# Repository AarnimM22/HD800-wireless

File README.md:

view online:
https://kicanvas.org/?repo=https%3A%2F%2Fgithub.com%2FAarnimM22%2FHD800-wireless

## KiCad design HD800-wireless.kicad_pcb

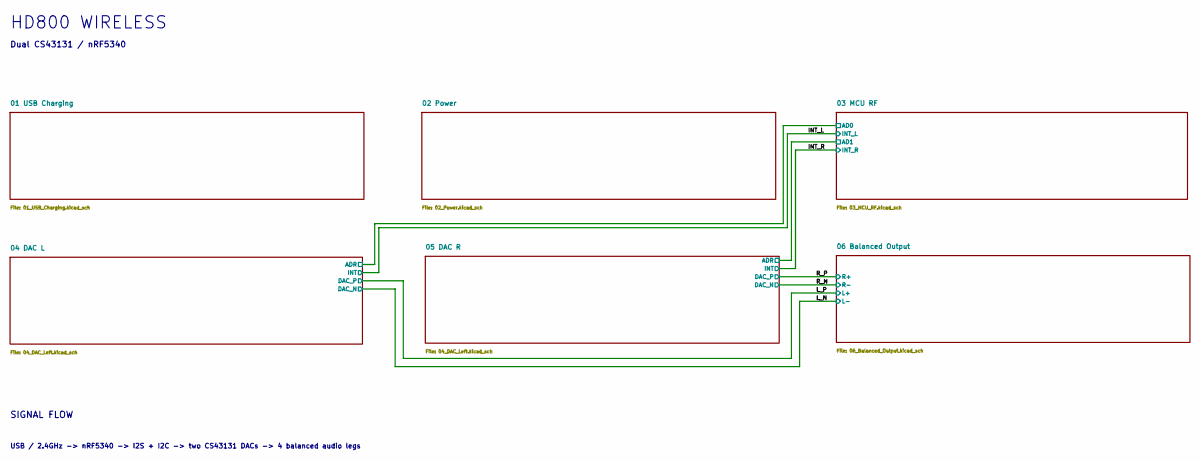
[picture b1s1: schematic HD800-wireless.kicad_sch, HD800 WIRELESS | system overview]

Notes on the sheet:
USB / 2.4GHz -> nRF5340 -> I2S + I2C -> two CS43131 DACs -> 4 balanced audio legs
Dual CS43131 / nRF5340
HD800 WIRELESS
SIGNAL FLOW

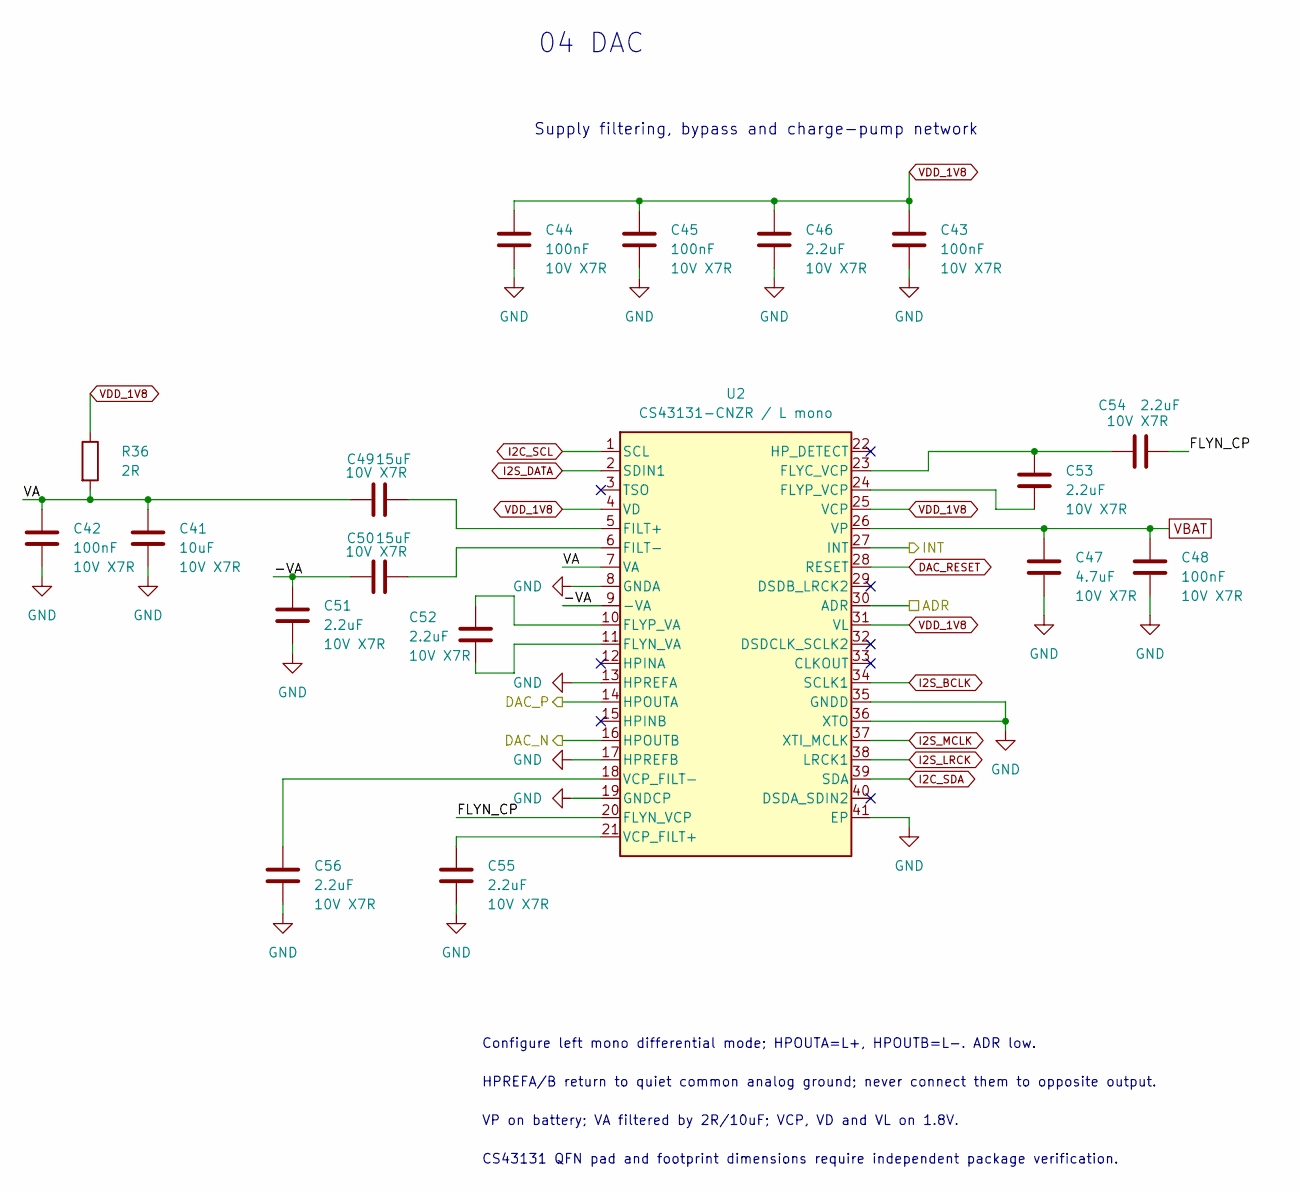
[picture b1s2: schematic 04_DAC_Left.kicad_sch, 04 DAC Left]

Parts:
C41: 10uF; C_0603_1608Metric; Voltage 10V X7R
C42, C43, C44, C45, C48: 100nF; C_0402_1005Metric; Voltage 10V X7R
C46, C51, C52, C53, C54, C55, C56: 2.2uF; C_0402_1005Metric; Voltage 10V X7R
C47: 4.7uF; C_0603_1608Metric; Voltage 10V X7R
C49, C50: 15uF; C_0603_1608Metric; Voltage 10V X7R
R36: 2R; R_0402_1005Metric
U2: CS43131-CNZR / L mono; TQFN-40-1EP_5x5mm_P0.4mm_EP3.5x3.5mm_ThermalVias

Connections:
/04 DAC L/-VA: C50.1, C51.1, U2.9 (-VA)
/04 DAC L/FLYN_CP: C54.2, U2.20 (FLYN_VCP)
/04 DAC L/VA: C41.1, C42.1, C49.1, R36.2, U2.7 (VA)
/INT_L: U2.27 (INT); also elsewhere on the board
/L_N: U2.16 (HPOUTB); also elsewhere on the board
/L_P: U2.14 (HPOUTA); also elsewhere on the board
DAC_RESET: U2.28 (RESET); also elsewhere on the board
GND: C41.2, C42.2, C43.2, C44.2, C45.2, C46.2, C47.2, C48.2, C51.2, C55.2, C56.2, U2.8 (GNDA), U2.13 (HPREFA), U2.17 (HPREFB), U2.19 (GNDCP), U2.30 (ADR), U2.35 (GNDD), U2.36 (XTO), U2.41 (EP); also elsewhere on the board
I2C_SCL: U2.1 (SCL); also elsewhere on the board
I2C_SDA: U2.39 (SDA); also elsewhere on the board
I2S_BCLK: U2.34 (SCLK1); also elsewhere on the board
I2S_DATA: U2.2 (SDIN1); also elsewhere on the board
I2S_LRCK: U2.38 (LRCK1); also elsewhere on the board
I2S_MCLK: U2.37 (XTI_MCLK); also elsewhere on the board
unnamed: C49.2, U2.5 (FILT+)
unnamed: C50.2, U2.6 (FILT-)
unnamed: C53.1, C54.1, U2.23 (FLYC_VCP)
unnamed: C52.2, U2.11 (FLYN_VA)
unnamed: C52.1, U2.10 (FLYP_VA)
unnamed: C53.2, U2.24 (FLYP_VCP)
unnamed: C55.1, U2.21 (VCP_FILT+)
unnamed: C56.1, U2.18 (VCP_FILT-)
VBAT: C47.1, C48.1, U2.26 (VP); also elsewhere on the board
VDD_1V8: C43.1, C44.1, C45.1, C46.1, R36.1, U2.4 (VD), U2.25 (VCP), U2.31 (VL); also elsewhere on the board

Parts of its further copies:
C57, C65, C66, C68, C72: 100nF; C_0402_1005Metric; Voltage 10V X7R
C58: 10uF; C_0603_1608Metric; Voltage 10V X7R
C59, C60, C63, C64, C67, C69, C71: 2.2uF; C_0402_1005Metric; Voltage 10V X7R
C61, C62: 15uF; C_0603_1608Metric; Voltage 10V X7R
C70: 4.7uF; C_0603_1608Metric; Voltage 10V X7R
R37: 2R; R_0402_1005Metric
U3: CS43131-CNZR / L mono; TQFN-40-1EP_5x5mm_P0.4mm_EP3.5x3.5mm_ThermalVias

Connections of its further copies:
/05 DAC R/-VA: C60.1, C62.1, U3.9 (-VA)
/05 DAC R/FLYN_CP: C71.2, U3.20 (FLYN_VCP)
/05 DAC R/VA: C57.1, C58.1, C61.1, R37.2, U3.7 (VA)
/INT_R: U3.27 (INT); also elsewhere on the board
/R_N: U3.16 (HPOUTB); also elsewhere on the board
/R_P: U3.14 (HPOUTA); also elsewhere on the board
DAC_RESET: U3.28 (RESET); also elsewhere on the board
GND: C57.2, C58.2, C59.2, C60.2, C63.2, C65.2, C66.2, C67.2, C68.2, C70.2, C72.2, U3.8 (GNDA), U3.13 (HPREFA), U3.17 (HPREFB), U3.19 (GNDCP), U3.35 (GNDD), U3.36 (XTO), U3.41 (EP); also elsewhere on the board
I2C_SCL: U3.1 (SCL); also elsewhere on the board
I2C_SDA: U3.39 (SDA); also elsewhere on the board
I2S_BCLK: U3.34 (SCLK1); also elsewhere on the board
I2S_DATA: U3.2 (SDIN1); also elsewhere on the board
I2S_LRCK: U3.38 (LRCK1); also elsewhere on the board
I2S_MCLK: U3.37 (XTI_MCLK); also elsewhere on the board
unnamed: C61.2, U3.5 (FILT+)
unnamed: C62.2, U3.6 (FILT-)
unnamed: C69.1, C71.1, U3.23 (FLYC_VCP)
unnamed: C64.2, U3.11 (FLYN_VA)
unnamed: C64.1, U3.10 (FLYP_VA)
unnamed: C69.2, U3.24 (FLYP_VCP)
unnamed: C63.1, U3.21 (VCP_FILT+)
unnamed: C59.1, U3.18 (VCP_FILT-)
VBAT: C70.1, C72.1, U3.26 (VP); also elsewhere on the board
VDD_1V8: C65.1, C66.1, C67.1, C68.1, R37.1, U3.4 (VD), U3.25 (VCP), U3.30 (ADR), U3.31 (VL); also elsewhere on the board

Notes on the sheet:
HPREFA/B return to quiet common analog ground; never connect them to opposite output.
Supply filtering, bypass and charge-pump network
Configure left mono differential mode; HPOUTA=L+, HPOUTB=L-. ADR low.
CS43131 QFN pad and footprint dimensions require independent package verification.
04 DAC
VP on battery; VA filtered by 2R/10uF; VCP, VD and VL on 1.8V.

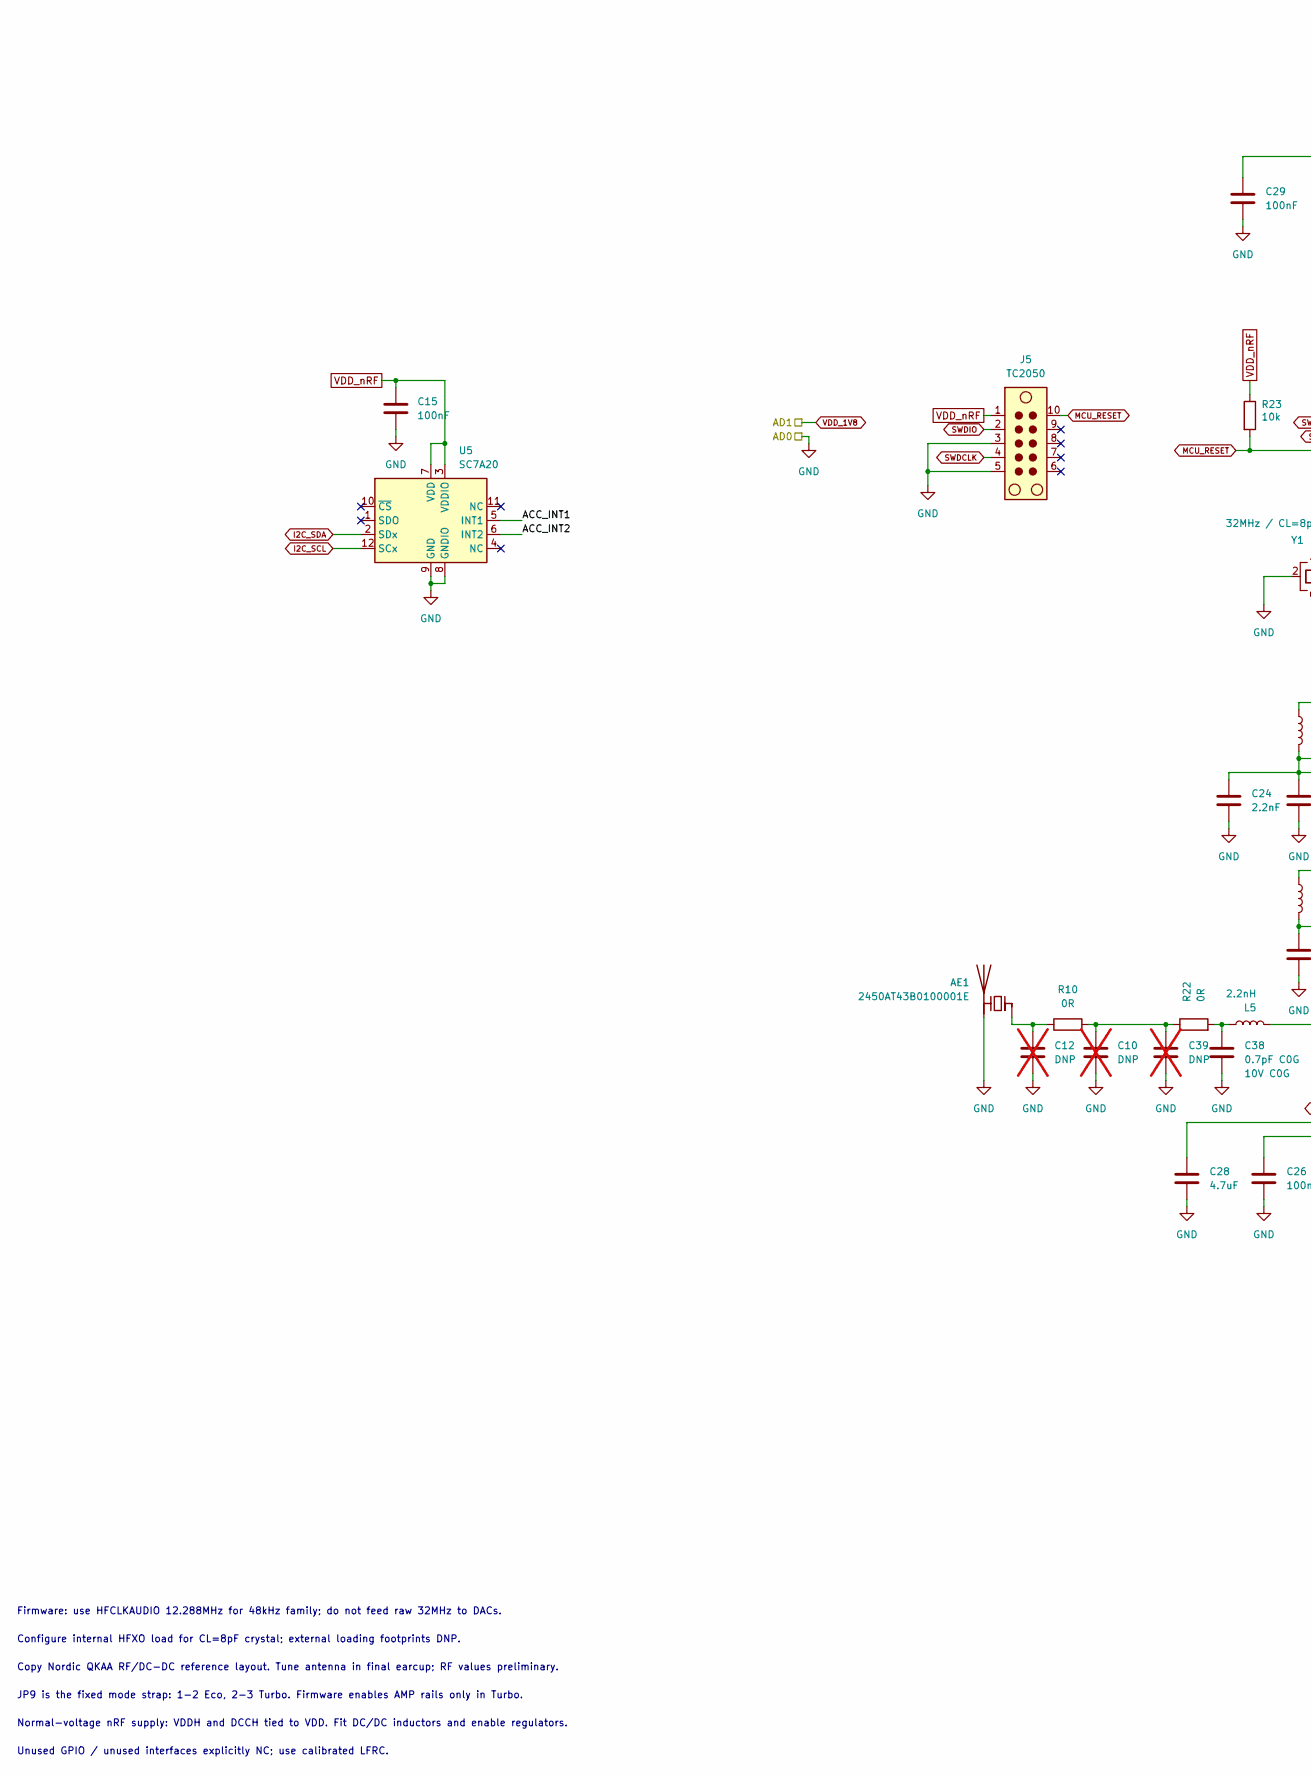
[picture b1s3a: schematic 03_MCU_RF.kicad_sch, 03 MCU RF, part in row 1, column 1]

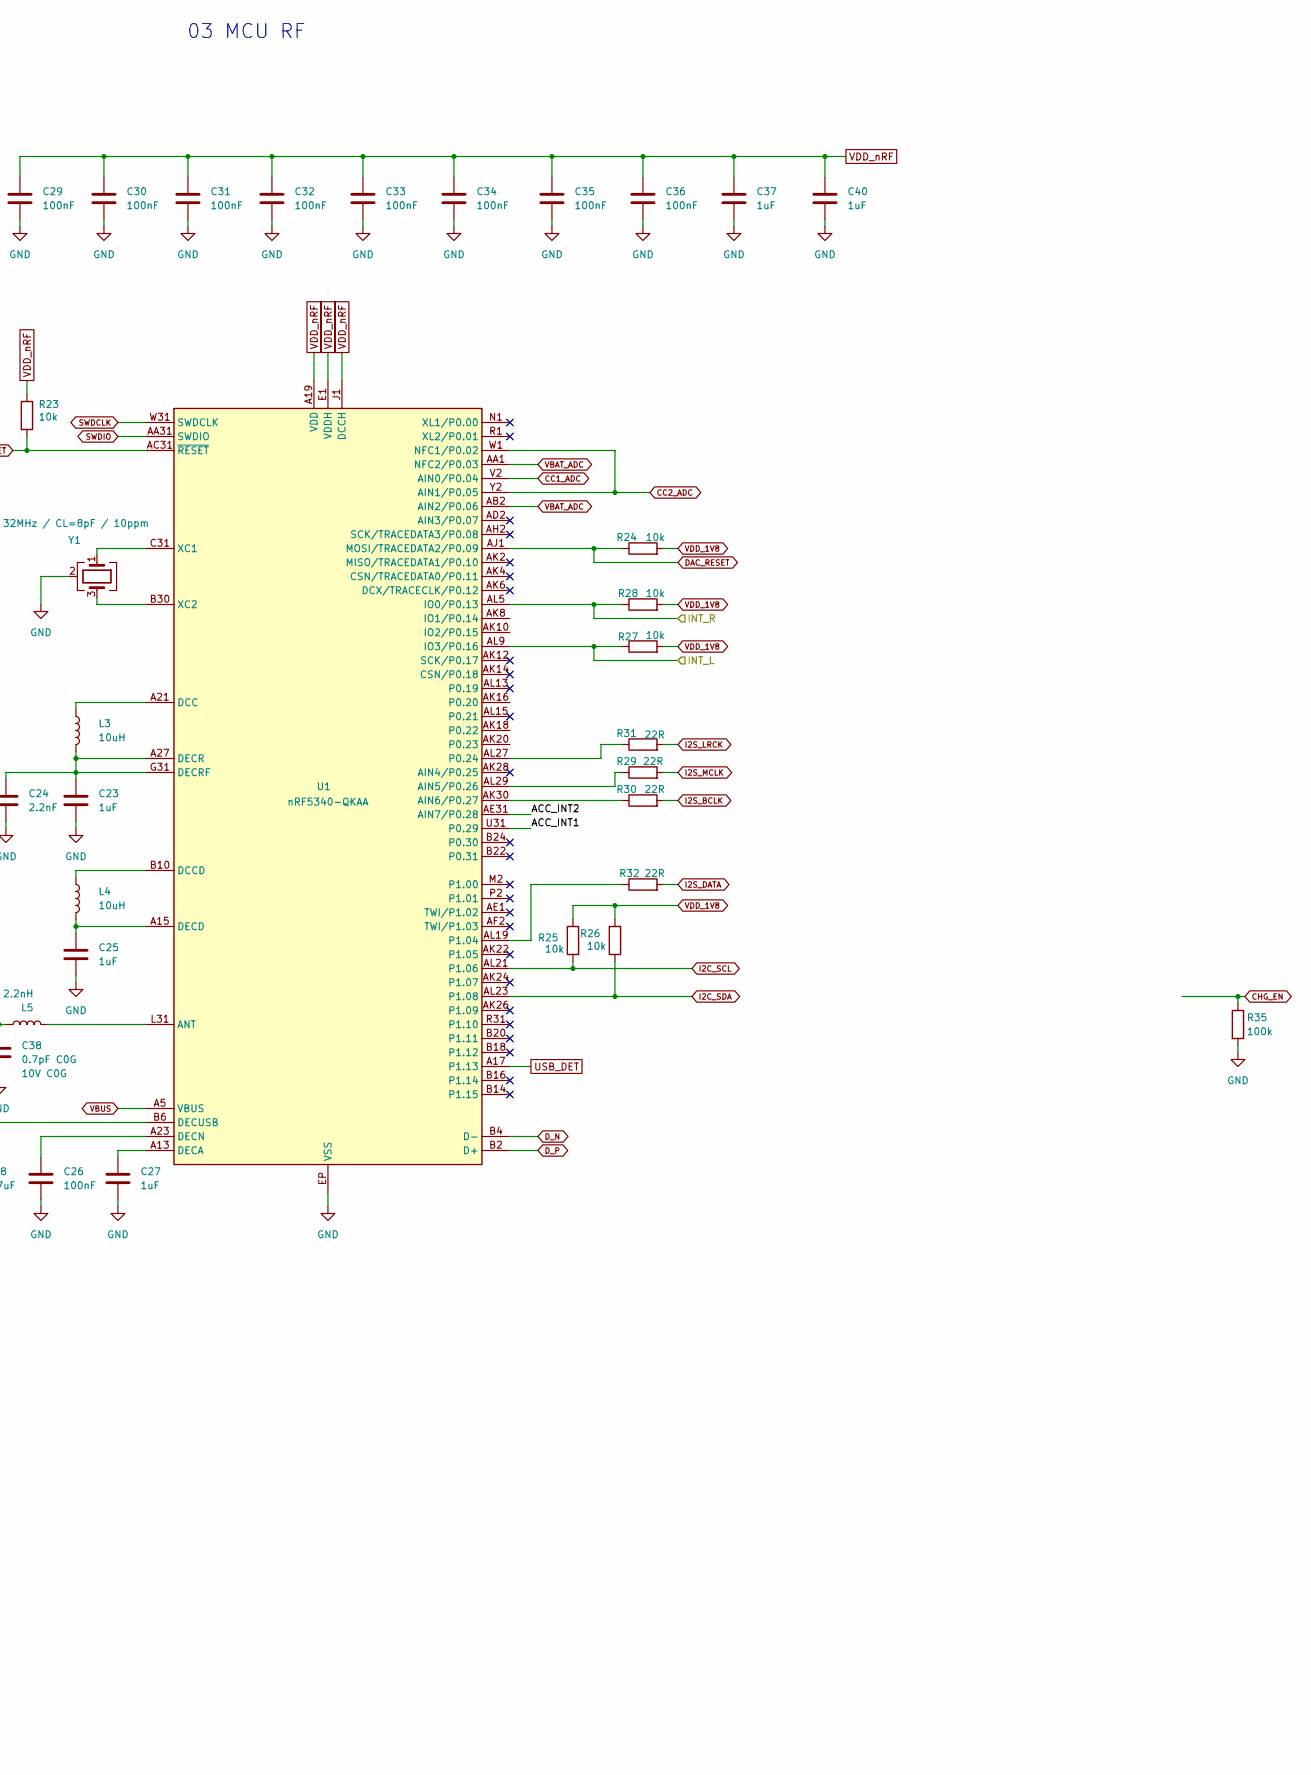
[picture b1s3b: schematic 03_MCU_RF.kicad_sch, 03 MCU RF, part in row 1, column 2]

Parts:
AE1: 2450AT43B0100001E; 2450AT18D0100
C10, C12, C39: DNP; C_0402_1005Metric; not fitted
C15, C26, C29, C30, C31, C32, C33, C34, C35, C36: 100nF; C_0402_1005Metric
C23, C25, C27, C37, C40: 1uF; C_0402_1005Metric
C24: 2.2nF; C_0402_1005Metric
C28: 4.7uF; C_0603_1608Metric
C38: 0.7pF C0G; C_0402_1005Metric; Voltage 10V C0G
J5: TC2050; Tag-Connect_TC2050-IDC-FP_2x05_P1.27mm_Vertical
L3, L4: 10uH; L_0603_1608Metric
L5: 2.2nH; L_0402_1005Metric
R10, R22: 0R; R_0402_1005Metric
R23, R24, R25, R26, R27, R28: 10k; R_0402_1005Metric
R29, R30, R31, R32: 22R; R_0402_1005Metric
R35: 100k; R_0402_1005Metric
U1: nRF5340-QKAA; Nordic_AQFN-94-1EP_7x7mm_P0.4mm
U5: SC7A20; LGA-12_2x2mm_P0.5mm
Y1: 32MHz / CL=8pF / 10ppm; Crystal_SMD_2016-4Pin_2.0x1.6mm

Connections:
/03 MCU RF/ACC_INT1: U1.U31 (P0.29), U5.5 (INT1)
/03 MCU RF/ACC_INT2: U1.AE31 (AIN7/P0.28), U5.6 (INT2)
/INT_L: R27.1, U1.AL9 (IO3/P0.16); also elsewhere on the board
/INT_R: R28.1, U1.AL5 (IO0/P0.13); also elsewhere on the board
CC1_ADC: U1.V2 (AIN0/P0.04); also elsewhere on the board
CC2_ADC: U1.W1 (NFC1/P0.02), U1.Y2 (AIN1/P0.05); also elsewhere on the board
CHG_EN: R35.1; also elsewhere on the board
DAC_RESET: R24.1, U1.AJ1 (MOSI/TRACEDATA2/P0.09); also elsewhere on the board
D_N: U1.B4 (D-); also elsewhere on the board
D_P: U1.B2 (D+); also elsewhere on the board
GND: AE1.2 (PCB_Trace), C10.2, C12.2, C15.2, C23.2, C24.2, C25.2, C26.2, C27.2, C28.2, C29.2, C30.2, C31.2, C32.2, C33.2, C34.2, C35.2, C36.2, C37.2, C38.2, C39.2, C40.2, J5.3, J5.5, R35.2, U1.EP (VSS), U5.8 (GNDIO), U5.9 (GND), Y1.2 (G), Y1.4 (G); also elsewhere on the board
I2C_SCL: R25.1, U1.AL21 (P1.06), U5.12 (SCx); also elsewhere on the board
I2C_SDA: R26.1, U1.AL23 (P1.08), U5.2 (SDx); also elsewhere on the board
I2S_BCLK: R30.2; also elsewhere on the board
I2S_DATA: R32.2; also elsewhere on the board
I2S_LRCK: R31.2; also elsewhere on the board
I2S_MCLK: R29.2; also elsewhere on the board
MCU_RESET: J5.10, R23.2, U1.AC31 (~RESET)
unnamed: AE1.1 (FEED), C12.1, R10.1
unnamed: C10.1, C39.1, R10.2, R22.1
unnamed: C38.1, L5.1, R22.2
unnamed: R29.1, U1.AL29 (AIN5/P0.26)
unnamed: R30.1, U1.AK30 (AIN6/P0.27)
unnamed: L5.2, U1.L31 (ANT)
unnamed: L3.1, U1.A21 (DCC)
unnamed: L4.1, U1.B10 (DCCD)
unnamed: C27.1, U1.A13 (DECA)
unnamed: C25.1, L4.2, U1.A15 (DECD)
unnamed: C26.1, U1.A23 (DECN)
unnamed: C23.1, C24.1, L3.2, U1.A27 (DECR), U1.G31 (DECRF)
unnamed: C28.1, U1.B6 (DECUSB)
unnamed: R31.1, U1.AL27 (P0.24)
unnamed: R32.1, U1.AL19 (P1.04)
unnamed: U1.C31 (XC1), Y1.1
unnamed: U1.B30 (XC2), Y1.3
SWDCLK: J5.4, U1.W31 (SWDCLK)
SWDIO: J5.2, U1.AA31 (SWDIO)
USB_DET: U1.A17 (P1.13); also elsewhere on the board
VBAT_ADC: U1.AA1 (NFC2/P0.03), U1.AB2 (AIN2/P0.06); also elsewhere on the board
VBUS: U1.A5 (VBUS); also elsewhere on the board
VDD_1V8: R24.2, R25.2, R26.2, R27.2, R28.2; also elsewhere on the board
VDD_nRF: C15.1, C29.1, C30.1, C31.1, C32.1, C33.1, C34.1, C35.1, C36.1, C37.1, C40.1, J5.1, R23.1, U1.A19 (VDD), U1.AC1 (VDD), U1.AG1 (VDD), U1.AJ31 (VDD), U1.AL3 (VDD), U1.AL7 (VDD), U1.AL11 (VDD), U1.AL17 (VDD), U1.AL25 (VDD), U1.B8 (VDD), U1.B28 (VDD), U1.C1 (VDD), U1.E1 (VDDH), U1.E31 (VDD), U1.J1 (DCCH), U1.L1 (VDD), U1.N31 (VDD), U1.U1 (VDD), U5.3 (VDDIO), U5.7 (VDD); also elsewhere on the board

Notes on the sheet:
Normal-voltage nRF supply: VDDH and DCCH tied to VDD. Fit DC/DC inductors and enable regulators.
Configure internal HFXO load for CL=8pF crystal; external loading footprints DNP.
Copy Nordic QKAA RF/DC-DC reference layout. Tune antenna in final earcup; RF values preliminary.
Unused GPIO / unused interfaces explicitly NC; use calibrated LFRC.
03 MCU RF
JP9 is the fixed mode strap: 1-2 Eco, 2-3 Turbo. Firmware enables AMP rails only in Turbo.
Firmware: use HFCLKAUDIO 12.288MHz for 48kHz family; do not feed raw 32MHz to DACs.

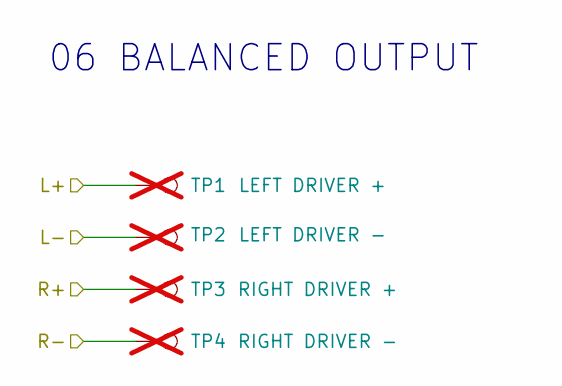
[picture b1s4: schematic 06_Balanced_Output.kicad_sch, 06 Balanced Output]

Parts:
TP1: LEFT DRIVER +; PinHeader_1x01_P2.00mm_Vertical; not fitted
TP2: LEFT DRIVER -; PinHeader_1x01_P2.00mm_Vertical; not fitted
TP3: RIGHT DRIVER +; PinHeader_1x01_P2.00mm_Vertical; not fitted
TP4: RIGHT DRIVER -; PinHeader_1x01_P2.00mm_Vertical; not fitted

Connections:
/L_N: TP2.1 (1_1); also elsewhere on the board
/L_P: TP1.1 (1_1); also elsewhere on the board
/R_N: TP4.1 (1_1); also elsewhere on the board
/R_P: TP3.1 (1_1); also elsewhere on the board

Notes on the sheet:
06 BALANCED OUTPUT

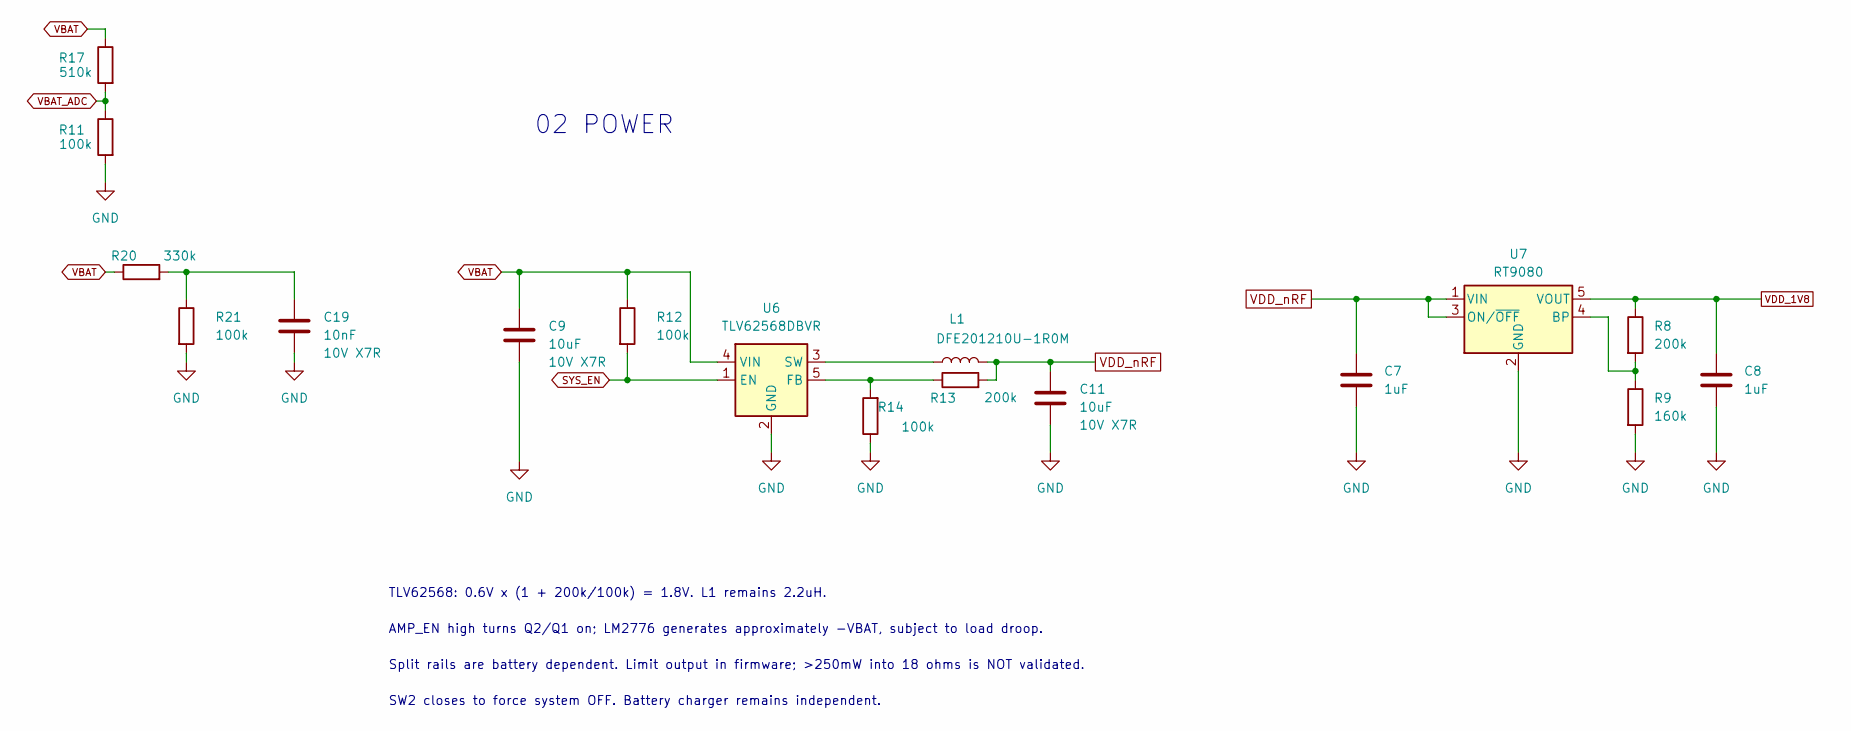
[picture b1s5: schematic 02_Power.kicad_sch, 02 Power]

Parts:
C7, C8: 1uF; C_0402_1005Metric
C9, C11: 10uF; C_0603_1608Metric; Voltage 10V X7R
C19: 10nF; C_0402_1005Metric; Voltage 10V X7R
L1: DFE201210U-1R0M; L_0805_2012Metric
R8, R13: 200k; R_0402_1005Metric
R9: 160k; R_0402_1005Metric
R11, R12, R14, R21: 100k; R_0402_1005Metric
R17: 510k; R_0402_1005Metric
R20: 330k; R_0402_1005Metric
U6: TLV62568DBVR; SOT-23-5
U7: RT9080; TSOT-23-5

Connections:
GND: C7.2, C8.2, C9.2, C11.2, C19.2, R9.2, R11.2, R14.1, R21.2, U6.2 (GND), U7.2 (GND); also elsewhere on the board
unnamed: C19.1, R20.2, R21.1
unnamed: R13.1, R14.2, U6.5 (FB)
unnamed: L1.1, U6.3 (SW)
unnamed: R8.2, R9.1, U7.4 (BP)
SYS_EN: R12.2, U6.1 (EN)
VBAT: C9.1, R12.1, R17.1, R20.1, U6.4 (VIN); also elsewhere on the board
VBAT_ADC: R11.1, R17.2; also elsewhere on the board
VDD_1V8: C8.1, R8.1, U7.5 (VOUT); also elsewhere on the board
VDD_nRF: C7.1, C11.1, L1.2, R13.2, U7.1 (VIN), U7.3 (ON/~OFF); also elsewhere on the board

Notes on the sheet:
02 POWER
AMP_EN high turns Q2/Q1 on; LM2776 generates approximately -VBAT, subject to load droop.
SW2 closes to force system OFF. Battery charger remains independent.
Split rails are battery dependent. Limit output in firmware; >250mW into 18 ohms is NOT validated.
TLV62568: 0.6V x (1 + 200k/100k) = 1.8V. L1 remains 2.2uH.

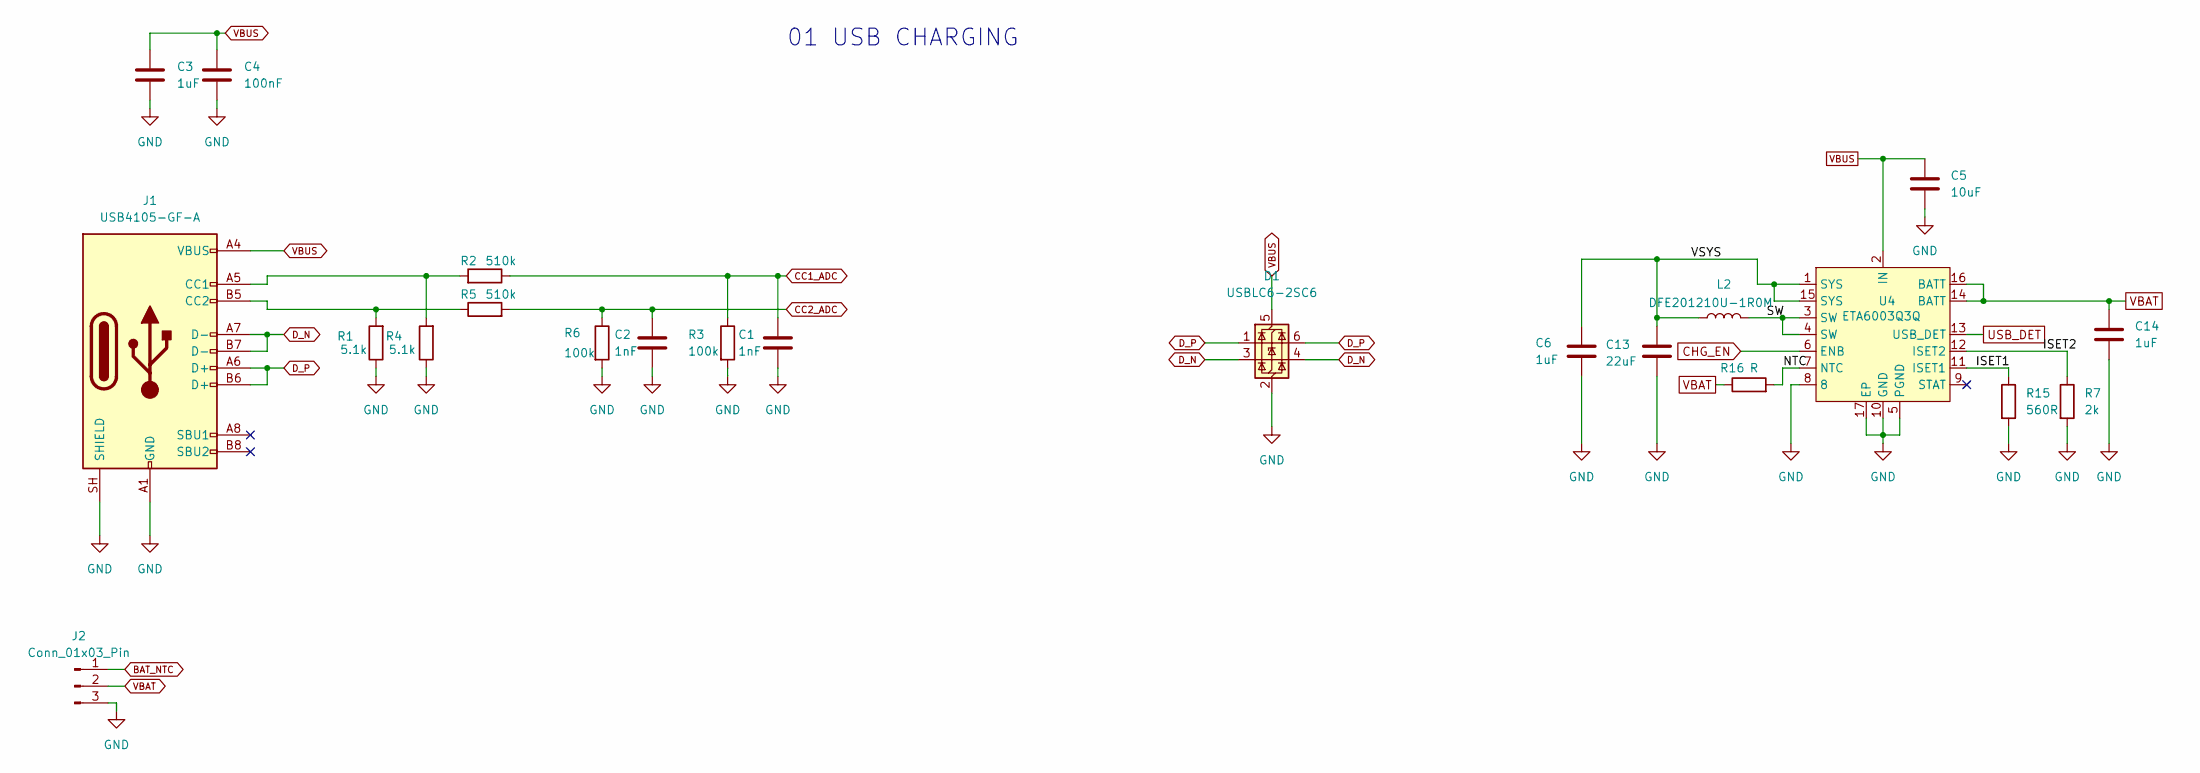
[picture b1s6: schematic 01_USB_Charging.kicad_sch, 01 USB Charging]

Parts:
C1, C2: 1nF; C_0402_1005Metric
C3, C6, C14: 1uF; C_0402_1005Metric
C4: 100nF; C_0402_1005Metric
C5: 10uF; C_0603_1608Metric
C13: 22uF; C_0603_1608Metric
D1: USBLC6-2SC6; SOT-23-6
J1: USB4105-GF-A; USB_C_Receptacle_GCT_USB4105-xx-A_16P_TopMnt_Horizontal
J2: Conn_01x03_Pin; JST_PH_S3B-PH-K_1x03_P2.00mm_Horizontal
L2: DFE201210U-1R0M; L_0805_2012Metric
R1, R4: 5.1k; R_0402_1005Metric
R2, R5: 510k; R_0402_1005Metric
R3, R6: 100k; R_0402_1005Metric
R7: 2k; R_0402_1005Metric
R15: 560R; R_0402_1005Metric
R16: R; R_0402_1005Metric
U4: ETA6003Q3Q; QFN-16-1EP_3x3mm_P0.5mm_EP1.7x1.7mm_ThermalVias

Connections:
/01 USB Charging/ISET1: R15.1, U4.11 (ISET1)
/01 USB Charging/ISET2: R7.1, U4.12 (ISET2)
/01 USB Charging/NTC: R16.2, U4.7 (NTC)
/01 USB Charging/SW: L2.2, U4.3 (SW), U4.4 (SW)
/01 USB Charging/VSYS: C6.1, C13.1, L2.1, U4.1 (SYS), U4.15 (SYS)
BAT_NTC: J2.1
CC1_ADC: C1.1, R2.1, R3.1; also elsewhere on the board
CC2_ADC: C2.1, R5.2, R6.1; also elsewhere on the board
CHG_EN: U4.6 (ENB); also elsewhere on the board
D_N: D1.3 (I/O2), D1.4 (I/O2), J1.A7 (D-), J1.B7 (D-); also elsewhere on the board
D_P: D1.1 (I/O1), D1.6 (I/O1), J1.A6 (D+), J1.B6 (D+); also elsewhere on the board
GND: C1.2, C2.2, C3.2, C4.2, C5.2, C6.2, C13.2, C14.1, D1.2 (GND), J1.A1 (GND), J1.A12 (GND), J1.B1 (GND), J1.B12 (GND), J1.SH (SHIELD), J2.3, R1.1, R3.2, R4.1, R6.2, R7.2, R15.2, U4.5 (PGND), U4.8, U4.10 (GND), U4.17 (EP); also elsewhere on the board
unnamed: J1.A5 (CC1), R2.2, R4.2
unnamed: J1.B5 (CC2), R1.2, R5.1
USB_DET: U4.13 (USB_DET); also elsewhere on the board
VBAT: C14.2, J2.2, R16.1, U4.14 (BATT), U4.16 (BATT); also elsewhere on the board
VBUS: C3.1, C4.1, C5.1, D1.5 (VBUS), J1.A4 (VBUS), J1.A9 (VBUS), J1.B4 (VBUS), J1.B9 (VBUS), U4.2 (IN); also elsewhere on the board

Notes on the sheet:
01 USB CHARGING

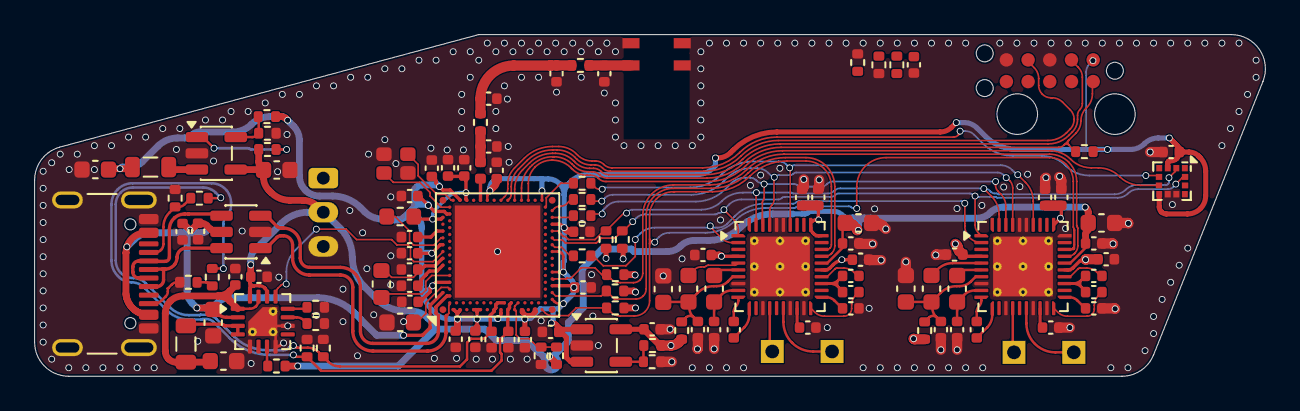
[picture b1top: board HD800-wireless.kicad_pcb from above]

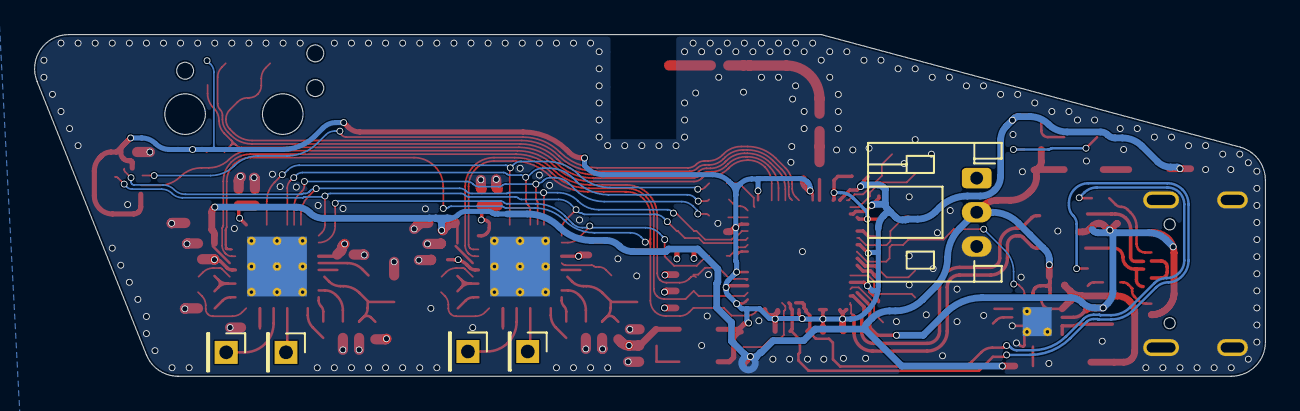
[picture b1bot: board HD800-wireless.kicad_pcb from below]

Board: 4 copper layers, 72.0 x 20.0 mm, 121 parts (5 on the bottom side), 81 nets.

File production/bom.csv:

Designator,Footprint,Quantity,Value,LCSC Part #
AE1,2450AT18D0100,1,2450AT43B0100001E,
"C1, C2",0402,2,1nF,
"C11, C41, C5, C58, C9",0603,5,10uF,
C13,0603,1,22uF,
"C14, C23, C25, C27, C3, C6, C7, C8",0402,8,1uF,
"C15, C26, C29, C30, C31, C32, C33, C34, C35, C36, C4, C42, C43, C44, C45, C48, C57, C65, C66, C68, C72",0402,21,100nF,
C19,0402,1,10nF,
C24,0402,1,2.2nF,
"C28, C47, C70",0603,3,4.7uF,
"C37, C40",0603,2,1uF,
C38,0402,1,0.7pF C0G,
"C46, C51, C52, C53, C54, C55, C56, C59, C60, C63, C64, C67, C69, C71",0402,14,2.2uF,
"C49, C50, C61, C62",0603,4,15uF,
D1,SOT-23-6,1,USBLC6-2SC6,
J1,USB_C_Receptacle_GCT_USB4105-xx-A_16P_TopMnt_Horizontal,1,USB4105-GF-A,
J2,JST_PH_S3B-PH-K_1x03_P2.00mm_Horizontal,1,Conn_01x03_Pin,
L1,0805,1,2.2uH DFE201210U-1R0M=P2,
L2,0805,1,DFE201210U-1R0M,
"L3, L4",0603,2,10uH,
L5,0402,1,2.2nH,
"R1, R4",0402,2,5.1k 1%,
"R10, R16",0402,2,R,
"R12, R35",0402,2,100k,
R13,0402,1,200k 1%,
"R14, R2, R21, R3, R5, R6",0402,6,100k 1%,
R15,0402,1,560R,
R20,0402,1,330k 1%,
R22,0402,1,0R,
"R23, R24",0402,2,10k,
"R25, R26, R27, R28",0402,4,4.7k,
"R29, R30, R31, R32",0402,4,22R,
"R36, R37",0402,2,2R 1%,
R7,0402,1,2k,
R8,0402,1,200k,
R9,0402,1,160k,
U1,Nordic_AQFN-94-1EP_7x7mm_P0.4mm,1,nRF5340-QKAA,
"U2, U3",TQFN-40-1EP_5x5mm_P0.4mm_EP3.5x3.5mm_ThermalVias,2,CS43131-CNZR / L mono,
U4,QFN-16-1EP_3x3mm_P0.5mm_EP1.7x1.7mm_ThermalVias,1,ETA6003Q3Q,
U5,LGA-12_2x2mm_P0.5mm,1,SC7A20,
U6,SOT-23-5,1,TLV62568DBVR,
U7,TSOT-23-5,1,RT9080,
Y1,Crystal_SMD_2016-4Pin_2.0x1.6mm,1,32MHz / CL=8pF / 10ppm,
